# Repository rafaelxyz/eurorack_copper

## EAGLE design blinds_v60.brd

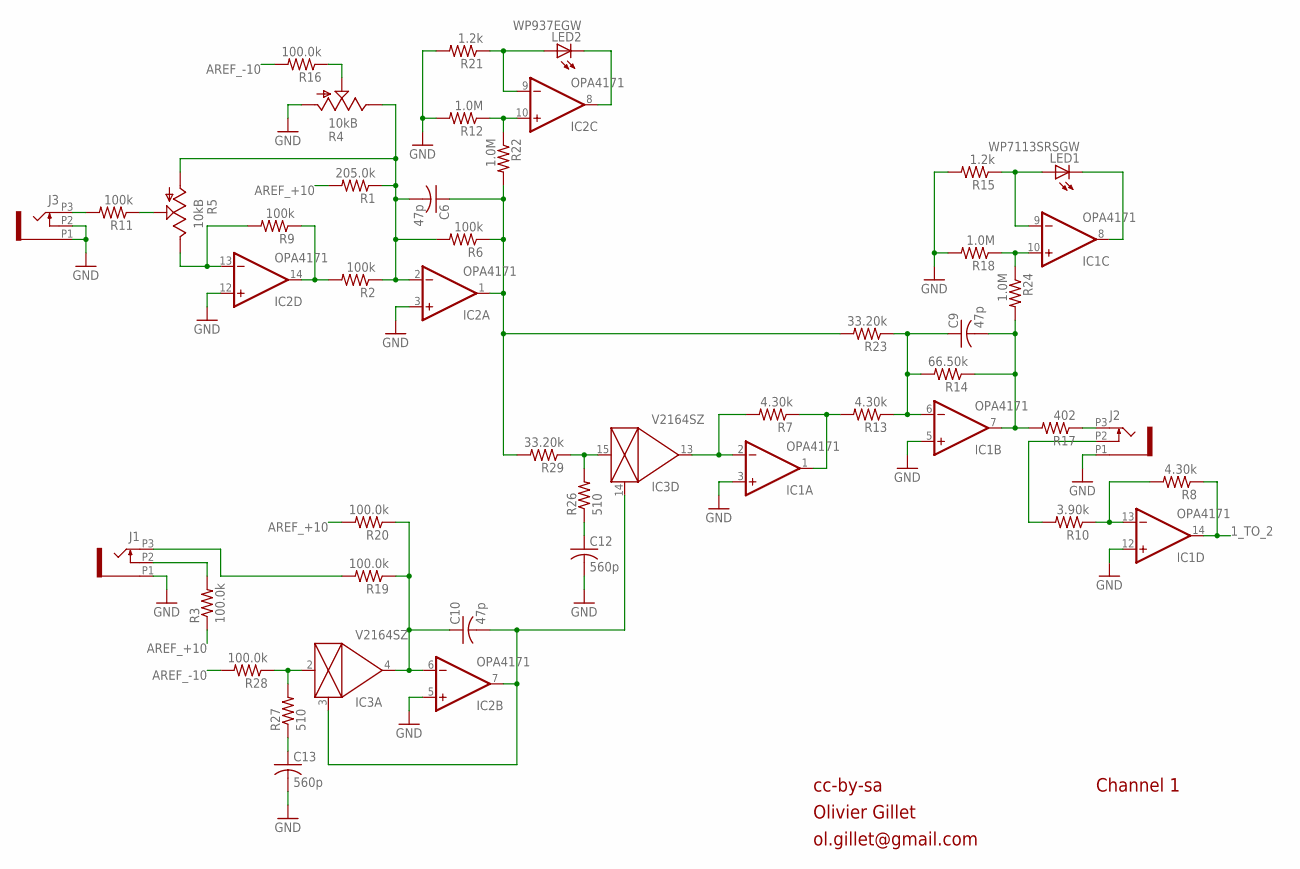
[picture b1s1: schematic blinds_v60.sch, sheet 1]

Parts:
C6, C9, C10: 47p; C0603
C12, C13: 560p; C0603
IC1, IC2: OPA4171; TSSOP14
IC3: V2164SZ; SOIC16N
J1, J2, J3: PJ301_THONKICONN6; WQP_PJ_301M6
LED1: WP7113SRSGW; LED5MM
LED2: WP937EGW; LED3MM
R1: 205.0k; R0603
R2, R6, R9, R11: 100k; R0603
R3, R16, R19, R20, R28: 100.0k; R0603
R4: 10kB; ALPS_POT_VERTICAL_PS
R5: 10kB; ALPS_POT_VERTICAL
R7, R8, R13: 4.30k; R0603
R10: 3.90k; R0603
R12, R18, R22, R24: 1.0M; R0603
R14: 66.50k; R0603
R15, R21: 1.2k; R0603
R17: 402; R0603
R23, R29: 33.20k; R0603
R26, R27: 510; R0603

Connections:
1_TO_2: IC1.14 (OUT), R8.1; also elsewhere on the board
AREF_+10: R1.2, R3.1, R20.2; also elsewhere on the board
AREF_-10: R16.2, R28.2; also elsewhere on the board
CV_IN_1: J3.P3 (3), R11.2
FOO: IC3.2 (IN), R27.2, R28.1
GAIN_1: C6.1, IC2.1 (OUT), R6.1, R22.2, R23.2, R29.2
GND: C12.2, C13.2, IC1.3 (+IN), IC1.5 (+IN), IC1.12 (+IN), IC2.3 (+IN), IC2.5 (+IN), IC2.12 (+IN), J1.P1 (1), J2.P1 (1), J3.P1 (1), J3.P2 (2), R4.P$3 (A), R12.2, R15.2, R18.2, R21.2; also elsewhere on the board
unnamed: R4.P$2 (S), R16.1
unnamed: IC1.2 (-IN), IC3.13 (OUT), R7.2
unnamed: IC2.8 (OUT), LED2.K (C)
unnamed: IC2.13 (-IN), R5.P$1 (E), R9.2
unnamed: J2.P3 (3), R17.1
unnamed: IC2.14 (OUT), R2.2, R9.1
unnamed: C6.2, IC2.2 (-IN), R1.1, R2.1, R4.P$1 (E), R5.P$3 (A), R6.2
unnamed: C9.1, IC1.6 (-IN), R13.1, R14.2, R23.1
unnamed: R5.P$2 (S), R11.1
unnamed: IC2.9 (-IN), LED2.A, R21.1
unnamed: IC1.8 (OUT), LED1.K (C)
unnamed: IC1.9 (-IN), LED1.A, R15.1
unnamed: C13.1, R27.1
unnamed: J1.P3 (3), R19.2
unnamed: IC1.13 (-IN), R8.2, R10.1
unnamed: J2.P2 (2), R10.2
unnamed: C12.1, R26.1
unnamed: J1.P2 (2), R3.2
unnamed: IC1.1 (OUT), R7.1, R13.2
unnamed: C10.1, IC2.6 (-IN), IC3.4 (OUT), R19.1, R20.1
unnamed: C10.2, IC2.7 (OUT), IC3.3 (CTRL), IC3.14 (CTRL)
unnamed: IC3.15 (IN), R26.2, R29.1
unnamed: IC1.10 (+IN), R18.1, R24.1
unnamed: IC2.10 (+IN), R12.1, R22.1
OUT1: C9.2, IC1.7 (OUT), R14.1, R17.2, R24.2

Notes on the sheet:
cc-by-sa
Olivier Gillet
ol.gillet@gmail.com
Channel 1

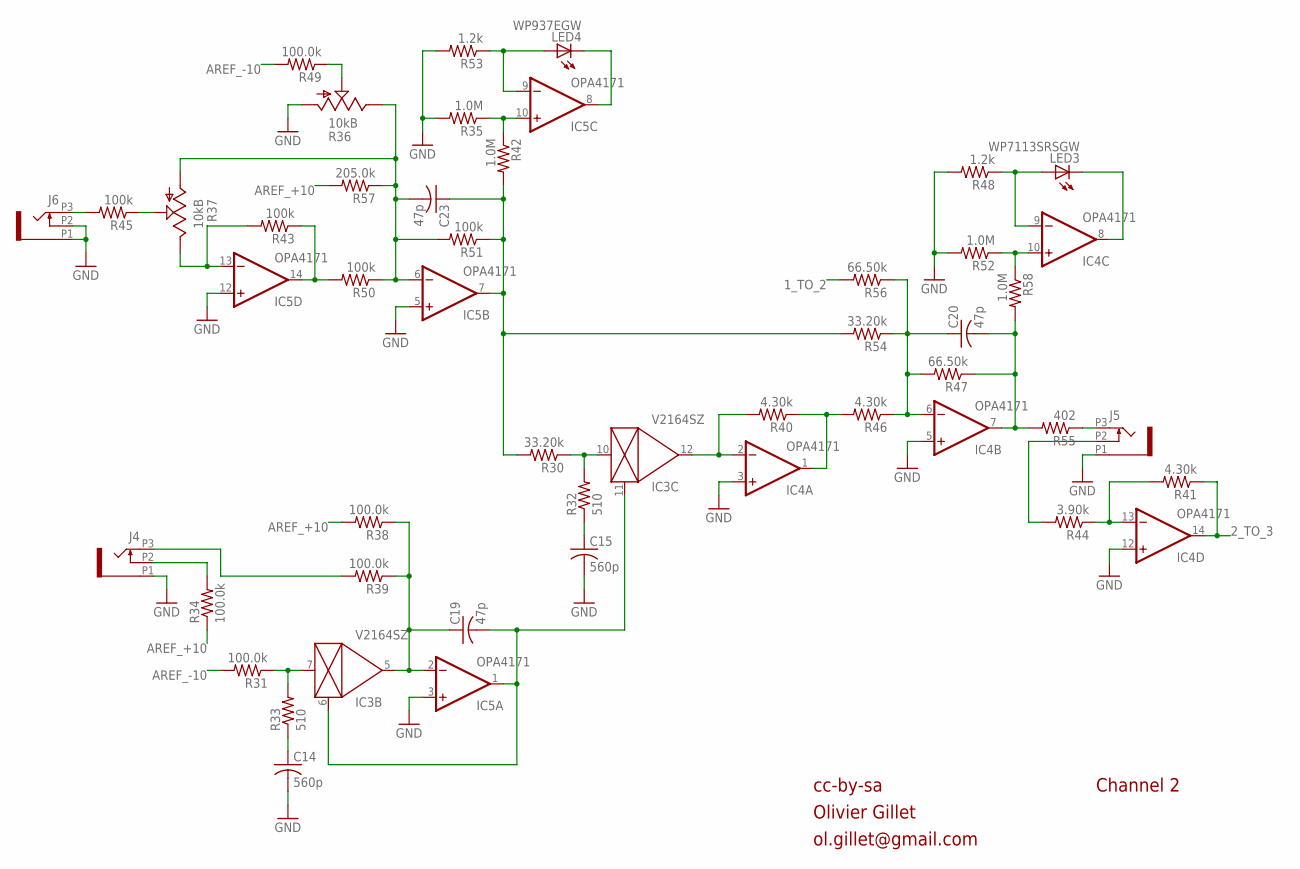
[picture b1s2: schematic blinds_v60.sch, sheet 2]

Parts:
C14, C15: 560p; C0603
C19, C20, C23: 47p; C0603
IC3: V2164SZ; SOIC16N
IC4, IC5: OPA4171; TSSOP14
J4, J5, J6: PJ301_THONKICONN6; WQP_PJ_301M6
LED3: WP7113SRSGW; LED5MM
LED4: WP937EGW; LED3MM
R30, R54: 33.20k; R0603
R31, R34, R38, R39, R49: 100.0k; R0603
R32, R33: 510; R0603
R35, R42, R52, R58: 1.0M; R0603
R36: 10kB; ALPS_POT_VERTICAL_PS
R37: 10kB; ALPS_POT_VERTICAL
R40, R41, R46: 4.30k; R0603
R43, R45, R50, R51: 100k; R0603
R44: 3.90k; R0603
R47, R56: 66.50k; R0603
R48, R53: 1.2k; R0603
R55: 402; R0603
R57: 205.0k; R0603

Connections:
1_TO_2: R56.2; also elsewhere on the board
2_TO_3: IC4.14 (OUT), R41.1; also elsewhere on the board
AREF_+10: R34.1, R38.2, R57.2; also elsewhere on the board
AREF_-10: R31.2, R49.2; also elsewhere on the board
FOO1: IC3.7 (IN), R31.1, R33.2
GAIN_2: C23.1, IC5.7 (OUT), R30.2, R42.2, R51.1, R54.2
GND: C14.2, C15.2, IC4.3 (+IN), IC4.5 (+IN), IC4.12 (+IN), IC5.3 (+IN), IC5.5 (+IN), IC5.12 (+IN), J4.P1 (1), J5.P1 (1), J6.P1 (1), J6.P2 (2), R35.2, R36.P$3 (A), R48.2, R52.2, R53.2; also elsewhere on the board
unnamed: J5.P3 (3), R55.1
unnamed: C15.1, R32.1
unnamed: IC3.10 (IN), R30.1, R32.2
unnamed: IC3.12 (OUT), IC4.2 (-IN), R40.2
unnamed: C20.1, IC4.6 (-IN), R46.1, R47.2, R54.1, R56.1
unnamed: J6.P3 (3), R45.2
unnamed: IC5.13 (-IN), R37.P$1 (E), R43.2
unnamed: IC5.14 (OUT), R43.1, R50.2
unnamed: C23.2, IC5.6 (-IN), R36.P$1 (E), R37.P$3 (A), R50.1, R51.2, R57.1
unnamed: R36.P$2 (S), R49.1
unnamed: IC5.8 (OUT), LED4.K (C)
unnamed: IC5.9 (-IN), LED4.A, R53.1
unnamed: IC4.8 (OUT), LED3.K (C)
unnamed: IC4.9 (-IN), LED3.A, R48.1
unnamed: IC4.13 (-IN), R41.2, R44.1
unnamed: J5.P2 (2), R44.2
unnamed: IC4.1 (OUT), R40.1, R46.2
unnamed: R37.P$2 (S), R45.1
unnamed: C14.1, R33.1
unnamed: C19.1, IC3.5 (OUT), IC5.2 (-IN), R38.1, R39.1
unnamed: C19.2, IC3.6 (CTRL), IC3.11 (CTRL), IC5.1 (OUT)
unnamed: J4.P3 (3), R39.2
unnamed: J4.P2 (2), R34.2
unnamed: IC4.10 (+IN), R52.1, R58.1
unnamed: IC5.10 (+IN), R35.1, R42.1
OUT2: C20.2, IC4.7 (OUT), R47.1, R55.2, R58.2

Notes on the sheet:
cc-by-sa
Olivier Gillet
ol.gillet@gmail.com
Channel 2

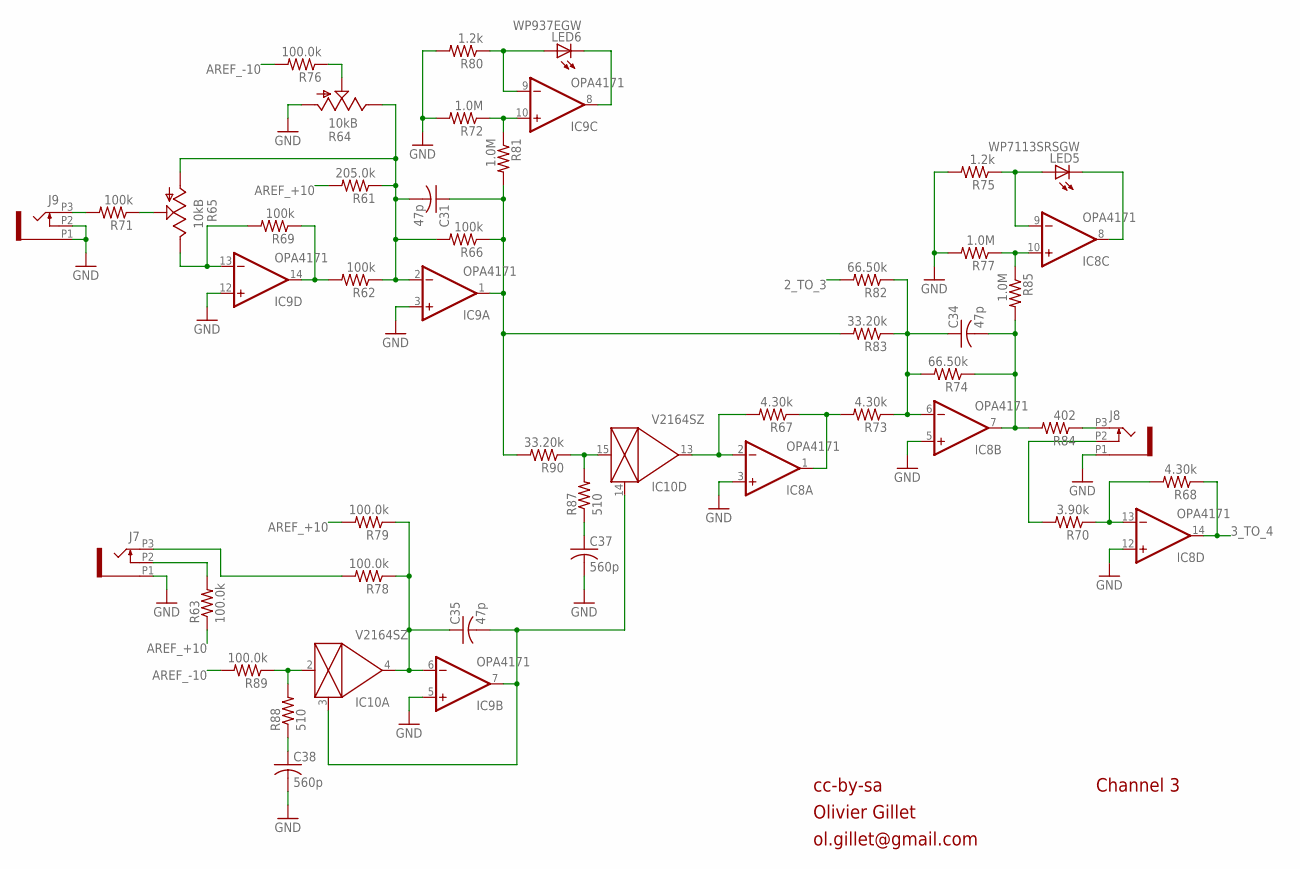
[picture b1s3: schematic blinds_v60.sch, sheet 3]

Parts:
C31, C34, C35: 47p; C0603
C37, C38: 560p; C0603
IC8, IC9: OPA4171; TSSOP14
IC10: V2164SZ; SOIC16N
J7, J8, J9: PJ301_THONKICONN6; WQP_PJ_301M6
LED5: WP7113SRSGW; LED5MM
LED6: WP937EGW; LED3MM
R61: 205.0k; R0603
R62, R66, R69, R71: 100k; R0603
R63, R76, R78, R79, R89: 100.0k; R0603
R64: 10kB; ALPS_POT_VERTICAL_PS
R65: 10kB; ALPS_POT_VERTICAL
R67, R68, R73: 4.30k; R0603
R70: 3.90k; R0603
R72, R77, R81, R85: 1.0M; R0603
R74, R82: 66.50k; R0603
R75, R80: 1.2k; R0603
R83, R90: 33.20k; R0603
R84: 402; R0603
R87, R88: 510; R0603

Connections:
2_TO_3: R82.2; also elsewhere on the board
3_TO_4: IC8.14 (OUT), R68.1; also elsewhere on the board
AREF_+10: R61.2, R63.1, R79.2; also elsewhere on the board
AREF_-10: R76.2, R89.2; also elsewhere on the board
FOO2: IC10.2 (IN), R88.2, R89.1
GAIN_3: C31.1, IC9.1 (OUT), R66.1, R81.2, R83.2, R90.2
GND: C37.2, C38.2, IC8.3 (+IN), IC8.5 (+IN), IC8.12 (+IN), IC9.3 (+IN), IC9.5 (+IN), IC9.12 (+IN), J7.P1 (1), J8.P1 (1), J9.P1 (1), J9.P2 (2), R64.P$3 (A), R72.2, R75.2, R77.2, R80.2; also elsewhere on the board
unnamed: J8.P3 (3), R84.1
unnamed: C37.1, R87.1
unnamed: IC10.15 (IN), R87.2, R90.1
unnamed: IC8.2 (-IN), IC10.13 (OUT), R67.2
unnamed: C34.1, IC8.6 (-IN), R73.1, R74.2, R82.1, R83.1
unnamed: J9.P3 (3), R71.2
unnamed: IC9.13 (-IN), R65.P$1 (E), R69.2
unnamed: IC9.14 (OUT), R62.2, R69.1
unnamed: C31.2, IC9.2 (-IN), R61.1, R62.1, R64.P$1 (E), R65.P$3 (A), R66.2
unnamed: R64.P$2 (S), R76.1
unnamed: IC9.8 (OUT), LED6.K (C)
unnamed: IC9.9 (-IN), LED6.A, R80.1
unnamed: IC8.8 (OUT), LED5.K (C)
unnamed: IC8.9 (-IN), LED5.A, R75.1
unnamed: IC8.13 (-IN), R68.2, R70.1
unnamed: J8.P2 (2), R70.2
unnamed: IC8.1 (OUT), R67.1, R73.2
unnamed: C38.1, R88.1
unnamed: C35.1, IC9.6 (-IN), IC10.4 (OUT), R78.1, R79.1
unnamed: C35.2, IC9.7 (OUT), IC10.3 (CTRL), IC10.14 (CTRL)
unnamed: R65.P$2 (S), R71.1
unnamed: J7.P3 (3), R78.2
unnamed: J7.P2 (2), R63.2
unnamed: IC8.10 (+IN), R77.1, R85.1
unnamed: IC9.10 (+IN), R72.1, R81.1
OUT3: C34.2, IC8.7 (OUT), R74.1, R84.2, R85.2

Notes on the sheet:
cc-by-sa
Olivier Gillet
ol.gillet@gmail.com
Channel 3

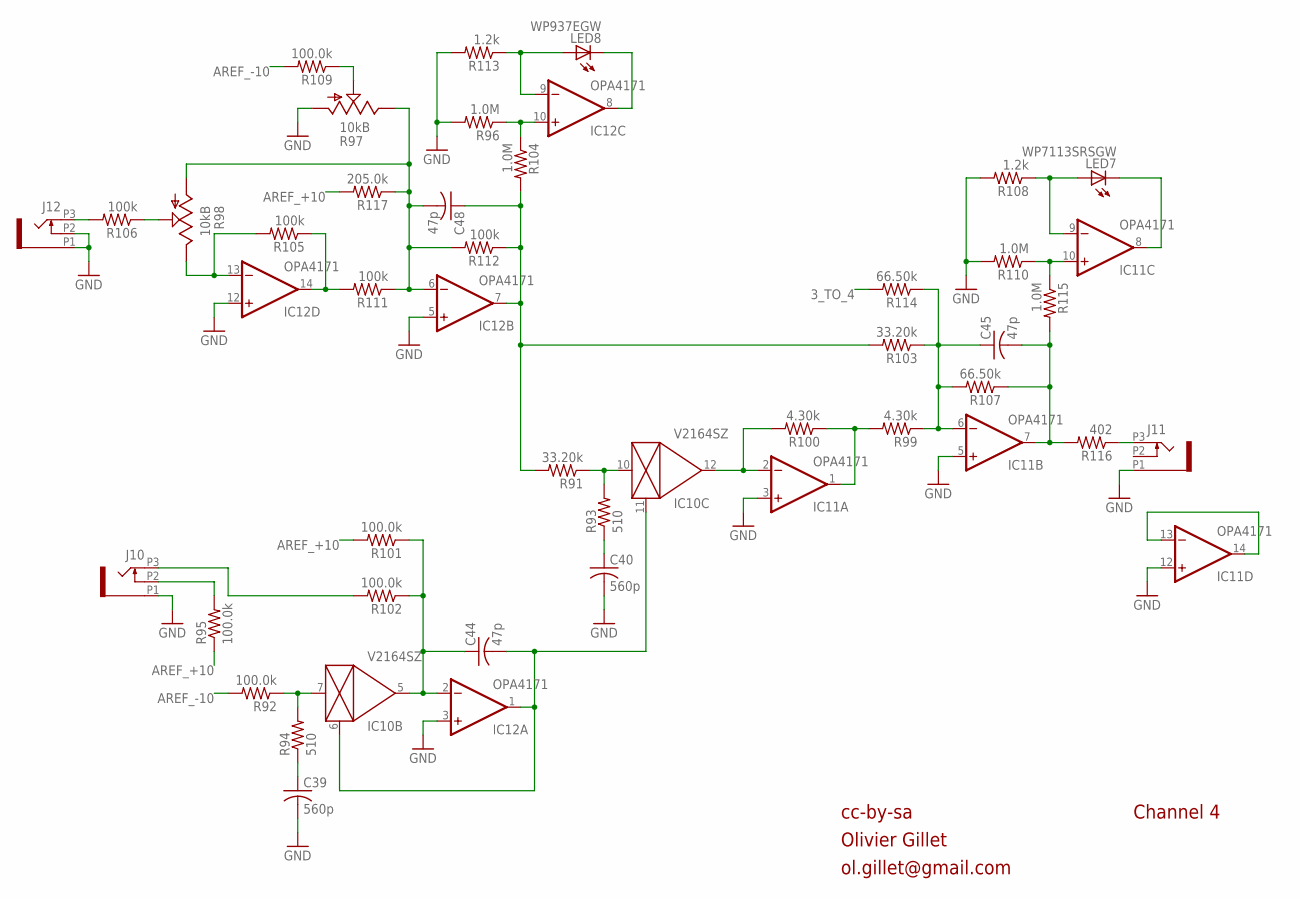
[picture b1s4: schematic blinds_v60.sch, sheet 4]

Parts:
C39, C40: 560p; C0603
C44, C45, C48: 47p; C0603
IC10: V2164SZ; SOIC16N
IC11, IC12: OPA4171; TSSOP14
J10, J11, J12: PJ301_THONKICONN6; WQP_PJ_301M6
LED7: WP7113SRSGW; LED5MM
LED8: WP937EGW; LED3MM
R91, R103: 33.20k; R0603
R92, R95, R101, R102, R109: 100.0k; R0603
R93, R94: 510; R0603
R96, R104, R110, R115: 1.0M; R0603
R97: 10kB; ALPS_POT_VERTICAL_PS
R98: 10kB; ALPS_POT_VERTICAL
R99, R100: 4.30k; R0603
R105, R106, R111, R112: 100k; R0603
R107, R114: 66.50k; R0603
R108, R113: 1.2k; R0603
R116: 402; R0603
R117: 205.0k; R0603

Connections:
3_TO_4: R114.2; also elsewhere on the board
AREF_+5: IC11.13 (-IN), IC11.14 (OUT)
AREF_+10: R95.1, R101.2, R117.2; also elsewhere on the board
AREF_-10: R92.2, R109.2; also elsewhere on the board
FOO3: IC10.7 (IN), R92.1, R94.2
GAIN_4: C48.1, IC12.7 (OUT), R91.2, R103.2, R104.2, R112.1
GND: C39.2, C40.2, IC11.3 (+IN), IC11.5 (+IN), IC11.12 (+IN), IC12.3 (+IN), IC12.5 (+IN), IC12.12 (+IN), J10.P1 (1), J11.P1 (1), J12.P1 (1), J12.P2 (2), R96.2, R97.P$3 (A), R108.2, R110.2, R113.2; also elsewhere on the board
unnamed: J10.P3 (3), R102.2
unnamed: J11.P3 (3), R116.1
unnamed: C40.1, R93.1
unnamed: IC10.10 (IN), R91.1, R93.2
unnamed: IC10.12 (OUT), IC11.2 (-IN), R100.2
unnamed: C45.1, IC11.6 (-IN), R99.1, R103.1, R107.2, R114.1
unnamed: J12.P3 (3), R106.2
unnamed: IC12.13 (-IN), R98.P$1 (E), R105.2
unnamed: IC12.14 (OUT), R105.1, R111.2
unnamed: C48.2, IC12.6 (-IN), R97.P$1 (E), R98.P$3 (A), R111.1, R112.2, R117.1
unnamed: R97.P$2 (S), R109.1
unnamed: IC12.8 (OUT), LED8.K (C)
unnamed: IC12.9 (-IN), LED8.A, R113.1
unnamed: IC11.8 (OUT), LED7.K (C)
unnamed: IC11.9 (-IN), LED7.A, R108.1
unnamed: IC11.1 (OUT), R99.2, R100.1
unnamed: R98.P$2 (S), R106.1
unnamed: C39.1, R94.1
unnamed: C44.1, IC10.5 (OUT), IC12.2 (-IN), R101.1, R102.1
unnamed: C44.2, IC10.6 (CTRL), IC10.11 (CTRL), IC12.1 (OUT)
unnamed: J10.P2 (2), R95.2
unnamed: IC11.10 (+IN), R110.1, R115.1
unnamed: IC12.10 (+IN), R96.1, R104.1
OUT4: C45.2, IC11.7 (OUT), R107.1, R115.2, R116.2

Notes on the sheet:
cc-by-sa
Olivier Gillet
ol.gillet@gmail.com
Channel 4

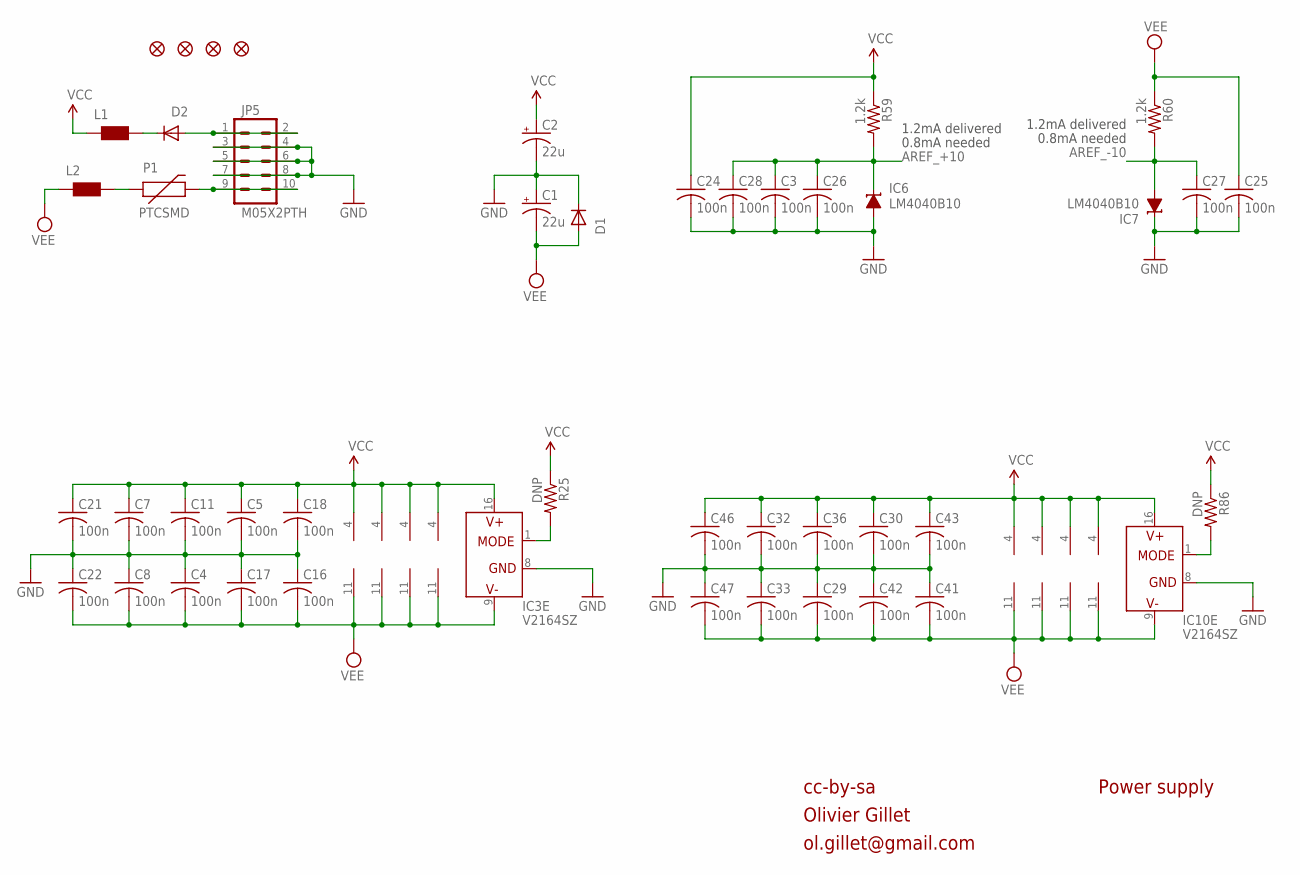
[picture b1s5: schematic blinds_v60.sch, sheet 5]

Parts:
C1, C2: 22u; PANASONIC_C
C3, C4, C5, C7, C8, C11, C16, C17, C18, C21, C22, C24, C25, C26, C27, C28, C29, C30, C32, C33, C36, C41, C42, C43, C46, C47: 100n; C0603
D1, D2: 1N5819HW; SOD123
IC1, IC2, IC4, IC5, IC8, IC9, IC11, IC12: OPA4171; TSSOP14
IC3, IC10: V2164SZ; SOIC16N
IC6, IC7: LM4040B10; DBZ_R-PDSO-G3
JP1, JP2, JP3, JP4: FIDUCIAL1X2; FIDUCIAL-1X2
JP5: M05X2PTH; AVR_ICSP
L1, L2: WE-CBF_0603; 0603
P1: PTCSMD; PTC-1206
R25, R86: DNP; R0603
R59, R60: 1.2k; R0603

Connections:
AREF_+10: C3.1, C26.1, C28.1, IC6.1 (C), R59.2; also elsewhere on the board
AREF_-10: C27.1, IC7.2 (A), R60.2; also elsewhere on the board
GND: C1.+, C2.-, C3.2, C4.1, C5.2, C7.2, C8.1, C11.2, C16.1, C17.1, C18.2, C21.2, C22.1, C24.2, C25.2, C26.2, C27.2, C28.2, C29.1, C30.2, C32.2, C33.1, C36.2, C41.1, C42.1, C43.2, C46.2, C47.1, D1.C, IC3.8 (GND), IC6.2 (A), IC7.1 (C), IC10.8 (GND), JP5.3, JP5.4, JP5.5, JP5.6, JP5.7, JP5.8; also elsewhere on the board
unnamed: IC3.1 (MODE), R25.2
unnamed: D2.A, JP5.1, JP5.2
unnamed: JP5.9, JP5.10, P1.2
unnamed: L2.2, P1.1
unnamed: D2.C, L1.2
unnamed: IC10.1 (MODE), R86.2
VCC: C2.+, C5.1, C7.1, C11.1, C18.1, C21.1, C24.1, C30.1, C32.1, C36.1, C43.1, C46.1, IC1.4 (V+), IC2.4 (V+), IC3.16 (V+), IC4.4 (V+), IC5.4 (V+), IC8.4 (V+), IC9.4 (V+), IC10.16 (V+), IC11.4 (V+), IC12.4 (V+), L1.1, R25.1, R59.1, R86.1
VEE: C1.-, C4.2, C8.2, C16.2, C17.2, C22.2, C25.1, C29.2, C33.2, C41.2, C42.2, C47.2, D1.A, IC1.11 (V-), IC2.11 (V-), IC3.9 (V-), IC4.11 (V-), IC5.11 (V-), IC8.11 (V-), IC9.11 (V-), IC10.9 (V-), IC11.11 (V-), IC12.11 (V-), L2.1, R60.1

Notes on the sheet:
cc-by-sa
Olivier Gillet
ol.gillet@gmail.com
Power supply
1.2mA delivered
0.8mA needed

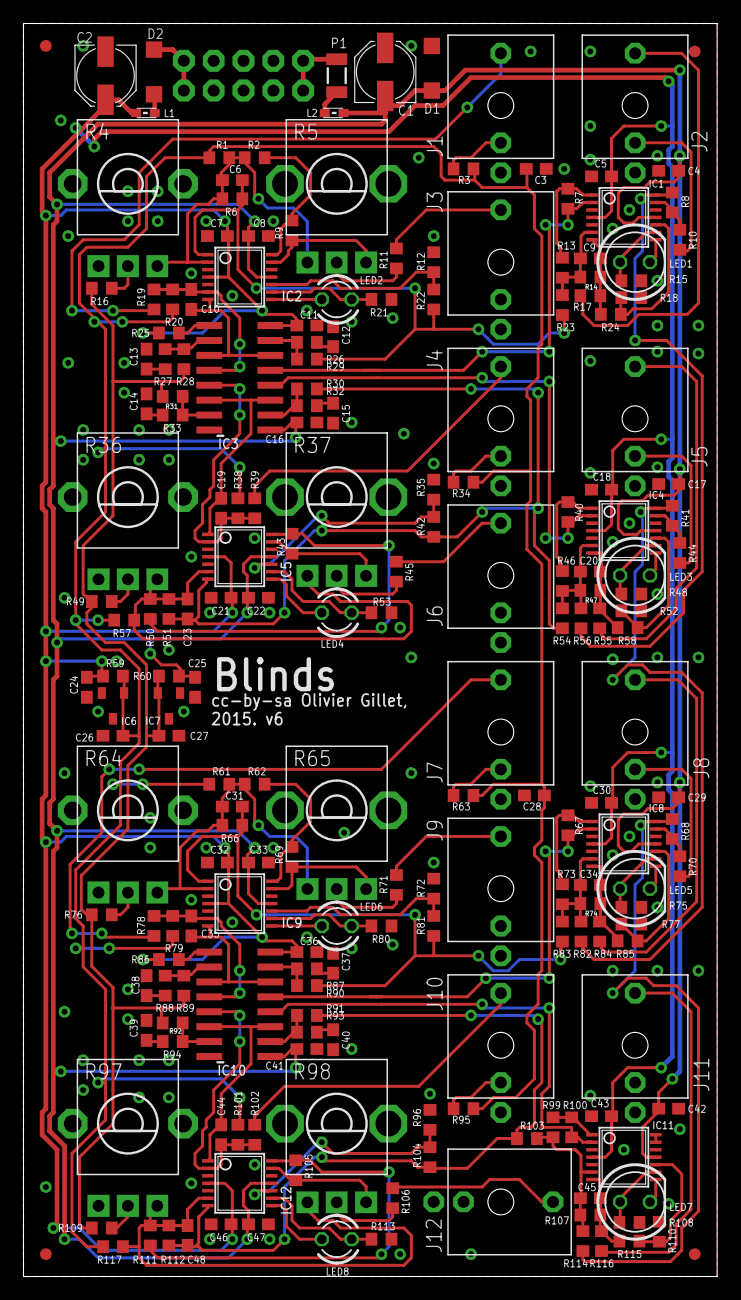
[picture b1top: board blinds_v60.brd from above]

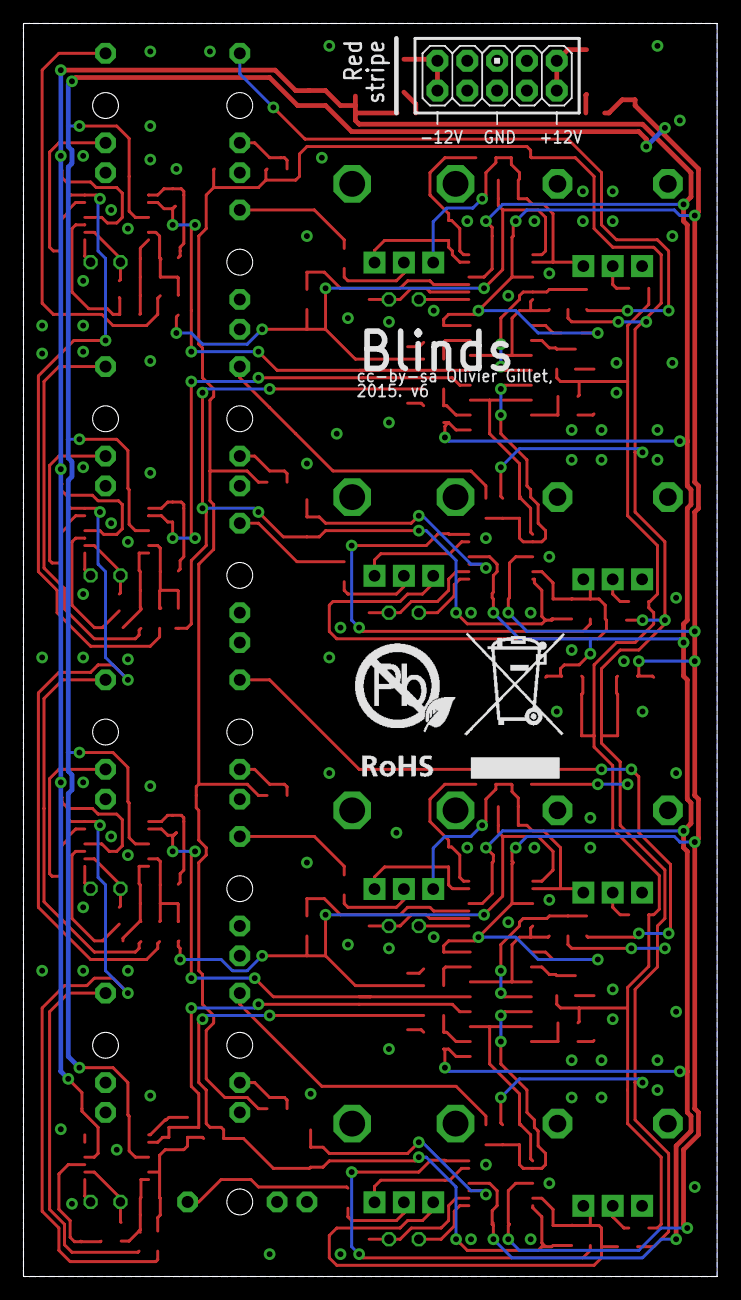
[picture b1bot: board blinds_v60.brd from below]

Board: 2 copper layers, 59.1 x 106.7 mm, 208 parts (2 on the bottom side), 125 nets.

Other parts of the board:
U$2: ROHS_BIG

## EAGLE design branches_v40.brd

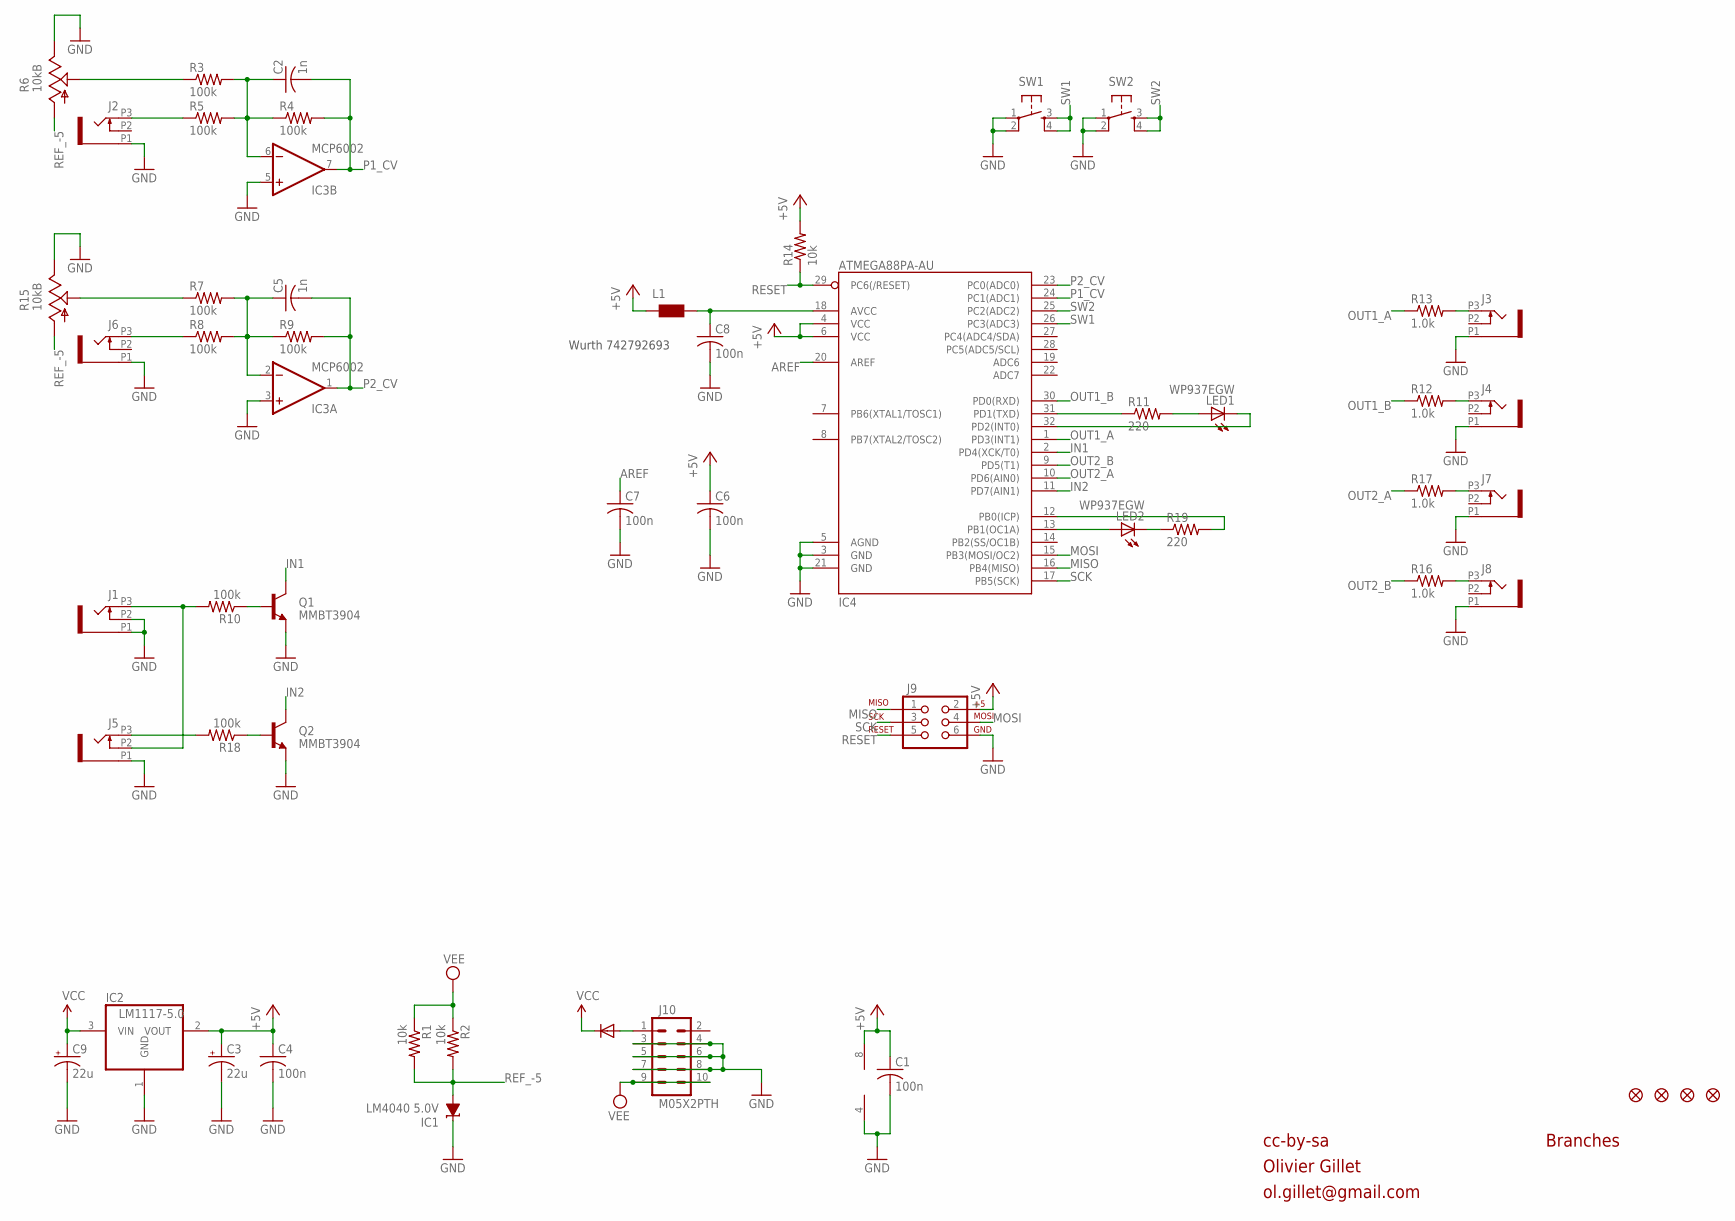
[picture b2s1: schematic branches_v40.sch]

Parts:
C1, C4, C6, C7, C8: 100n; C0603
C2, C5: 1n; C0603
C3, C9: 22u; PANASONIC_C
D1: 1N5819HW; SOD123
F1, F2, F3, F4: FIDUCIAL1X2; FIDUCIAL-1X2
IC1: LM4040 5.0V; DBZ_R-PDSO-G3
IC2: LM1117-5.0; SOT223
IC3: MCP6002; SO08
IC4: ATMEGA88PA-AU; TQFP32-08
J1, J2, J3, J4, J5, J6, J7, J8: PJ301_THONKICONN6; WQP_PJ_301M6
J9: AVR_SPI_PRG_6PTH; 2X3
J10: M05X2PTH; AVR_ICSP
L1: WE-CBF_0603; 0603
LED1, LED2: WP937EGW; LED3MM
Q1, Q2: MMBT3904; SOT23-BEC
R1, R2, R14: 10k; R0603
R3, R4, R5, R7, R8, R9, R10, R18: 100k; R0603
R6, R15: 10kB; ALPS_POT_VERTICAL_PS
R11, R19: 220; R0603
R12, R13, R16, R17: 1.0k; R0603
SW1, SW2: TAC_SWITCHPTH; TACTILE-PTH

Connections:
+5V: C1.1, C3.+, C4.1, C6.1, IC2.2 (VOUT), IC3.8 (V+), IC4.4 (VCC), IC4.6 (VCC), J9.2, L1.1, R14.2
AREF: C7.1, IC4.20 (AREF)
GATE1_IN: J1.P3 (3), J5.P2 (2), R10.2
GATE2_IN: J5.P3 (3), R18.2
GND: C1.2, C3.-, C4.2, C6.2, C7.2, C8.2, C9.-, IC1.1 (C), IC2.1 (GND), IC3.3 (+IN), IC3.4 (V-), IC3.5 (+IN), IC4.3 (GND), IC4.5 (AGND), IC4.21 (GND), J1.P1 (1), J1.P2 (2), J2.P1 (1), J3.P1 (1), J4.P1 (1), J5.P1 (1), J6.P1 (1), J7.P1 (1), J8.P1 (1), J9.6, J10.3, J10.4, J10.5, J10.6, J10.7, J10.8, Q1.E, Q2.E, R6.P$1 (E), R15.P$1 (E), SW1.1, SW1.2, SW2.1, SW2.2
IN1: IC4.2 (PD4(XCK/T0)), Q1.C
IN2: IC4.11 (PD7(AIN1)), Q2.C
MISO: IC4.16 (PB4(MISO)), J9.1
MOSI: IC4.15 (PB3(MOSI/OC2)), J9.4
unnamed: Q1.B, R10.1
unnamed: Q2.B, R18.1
unnamed: D1.A, J10.1
unnamed: C5.1, IC3.2 (-IN), R7.2, R8.2, R9.1
unnamed: J8.P3 (3), R16.2
unnamed: R7.1, R15.P$2 (S)
unnamed: R3.1, R6.P$2 (S)
unnamed: J2.P3 (3), R5.1
unnamed: J6.P3 (3), R8.1
unnamed: IC4.31 (PD1(TXD)), R11.1
unnamed: LED1.A, R11.2
unnamed: IC4.32 (PD2(INT0)), LED1.K (C)
unnamed: IC4.13 (PB1(OC1A)), LED2.A
unnamed: LED2.K (C), R19.1
unnamed: IC4.12 (PB0(ICP)), R19.2
unnamed: C2.1, IC3.6 (-IN), R3.2, R4.1, R5.2
unnamed: J3.P3 (3), R13.2
unnamed: J4.P3 (3), R12.2
unnamed: J7.P3 (3), R17.2
unnamed: C8.1, IC4.18 (AVCC), L1.2
OUT1_A: IC4.1 (PD3(INT1)), R13.1
OUT1_B: IC4.30 (PD0(RXD)), R12.1
OUT2_A: IC4.10 (PD6(AIN0)), R17.1
OUT2_B: IC4.9 (PD5(T1)), R16.1
P1_CV: C2.2, IC3.7 (OUT), IC4.24 (PC1(ADC1)), R4.2
P2_CV: C5.2, IC3.1 (OUT), IC4.23 (PC0(ADC0)), R9.2
REF_-5: IC1.2 (A), R1.2, R2.2, R6.P$3 (A), R15.P$3 (A)
RESET: IC4.29 (PC6(/RESET)), J9.5, R14.1
SCK: IC4.17 (PB5(SCK)), J9.3
SW1: IC4.26 (PC3(ADC3)), SW1.3, SW1.4
SW2: IC4.25 (PC2(ADC2)), SW2.3, SW2.4
VCC: C9.+, D1.C, IC2.3 (VIN)
VEE: J10.9, J10.10, R1.1, R2.1

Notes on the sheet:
cc-by-sa
Olivier Gillet
ol.gillet@gmail.com
Branches
Wurth 742792693

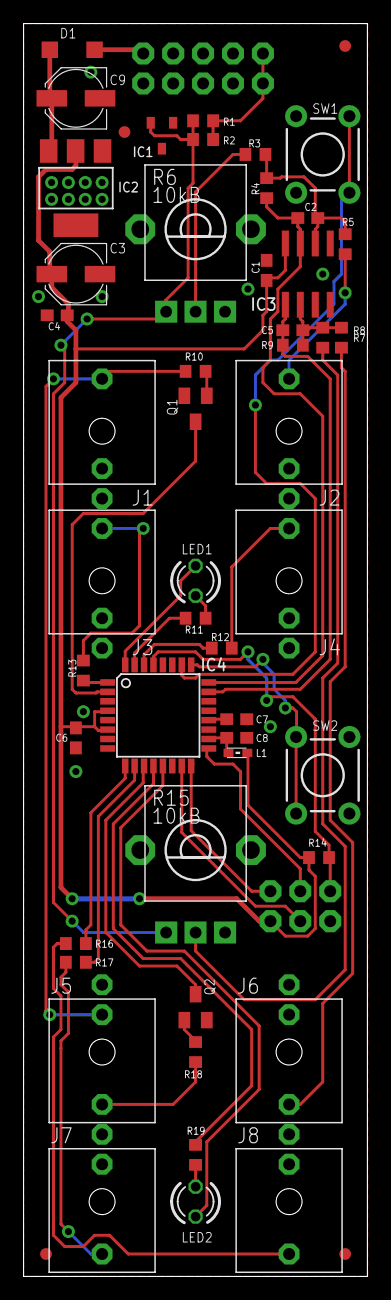
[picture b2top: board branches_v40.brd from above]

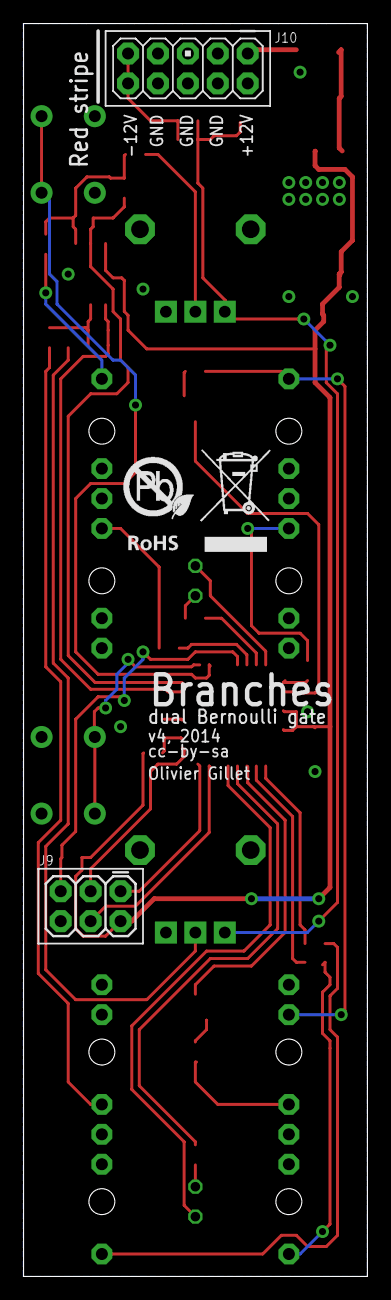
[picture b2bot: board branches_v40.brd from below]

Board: 2 copper layers, 29.2 x 106.4 mm, 55 parts (3 on the bottom side), 42 nets.

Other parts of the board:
U$1: ROHS

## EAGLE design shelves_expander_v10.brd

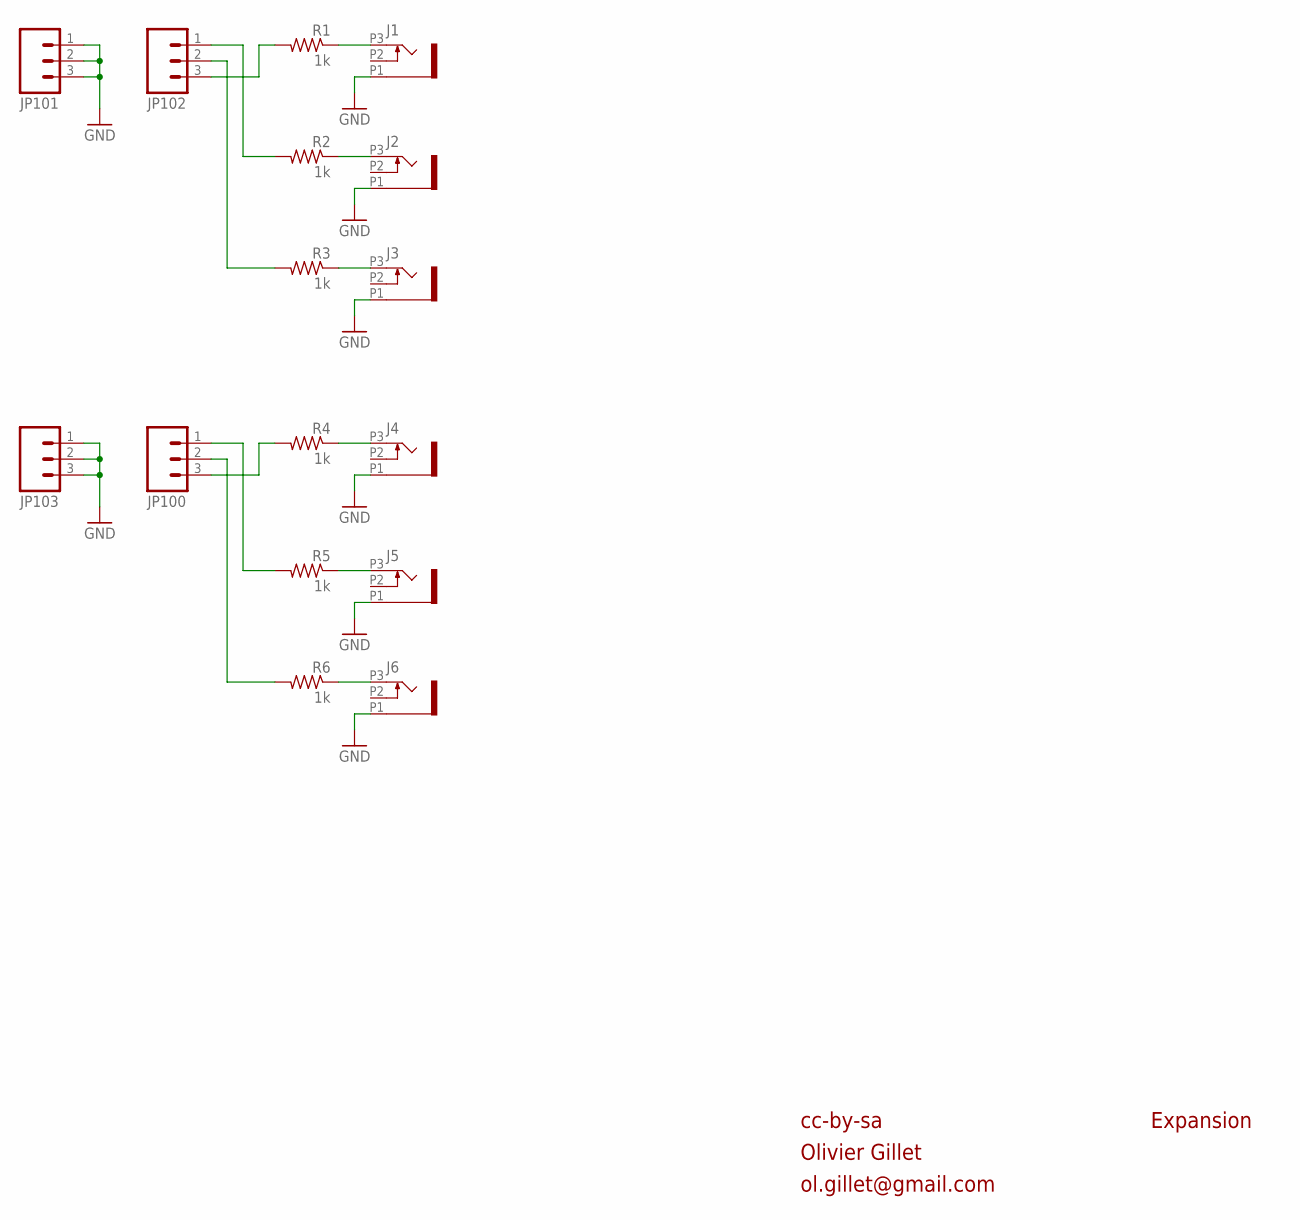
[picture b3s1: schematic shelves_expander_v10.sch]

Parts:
J1, J2, J3, J4, J5, J6: PJ301_THONKICONN6; WQP_PJ_301M6
JP100, JP101, JP102, JP103: M03PTH; 1X03
R1, R2, R3, R4, R5, R6: 1k; R0603

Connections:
BP_1: JP102.1, R2.2
BP_2: JP100.1, R5.2
GND: J1.P1 (1), J2.P1 (1), J3.P1 (1), J4.P1 (1), J5.P1 (1), J6.P1 (1), JP101.1, JP101.2, JP101.3, JP103.1, JP103.2, JP103.3
HP_1: JP102.3, R1.2
HP_2: JP100.3, R4.2
unnamed: J4.P3 (3), R4.1
unnamed: J1.P3 (3), R1.1
unnamed: J6.P3 (3), R6.1
unnamed: J2.P3 (3), R2.1
unnamed: J5.P3 (3), R5.1
unnamed: J3.P3 (3), R3.1
unnamed: JP100.2, R6.2
unnamed: JP102.2, R3.2

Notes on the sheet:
cc-by-sa
Olivier Gillet
ol.gillet@gmail.com
Expansion

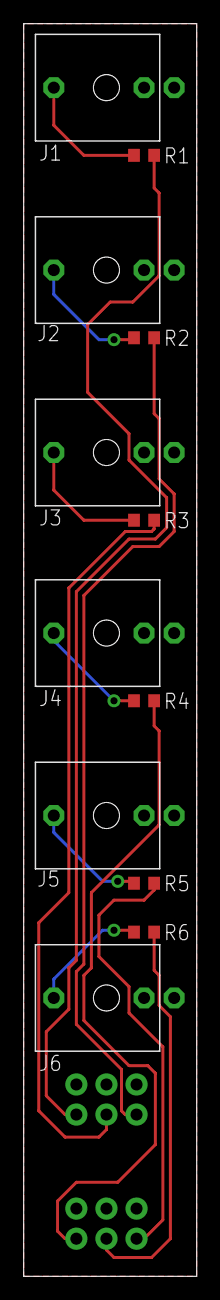
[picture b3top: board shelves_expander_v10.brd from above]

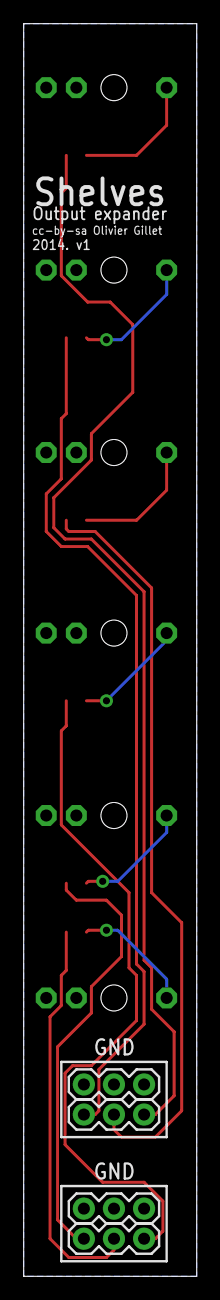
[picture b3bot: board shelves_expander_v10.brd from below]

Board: 2 copper layers, 14.6 x 105.7 mm, 16 parts (4 on the bottom side), 13 nets.

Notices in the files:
braids_v50.brd:
cc-by-sa Olivier Gillet, 2015. v5
shelves_v05.brd:
cc-by-sa Olivier Gillet, 2014. v0.5
streams_v02_bargraph.brd:
cc-by-sa Olivier Gillet, 2014. v0.2
warps_v30.brd:
cc-by-sa Olivier Gillet, 2015. v3
